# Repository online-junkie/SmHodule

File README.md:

# SmHodule

SmHodule is using the Wifi SoC ESP8266, the ESP8266 is a System on Chip and is as powerful as an Arduino.

SmHodule = Smart Home module for the Internet of Things.

This module is based on a set of examples found in the Internet about ESP8266 and implementing a actor, sender, sensor and I2C OLED.

The Setup data is cached in the modules flash memory.

Feel free to expand SmHodule and add your own ideas.

## Compile

Compile the code, then: make clean, make html, make all, make flashall
 
For first time setup keep GPIO15 pulled to ground for 35 seconds.
After first time configuration the module reboots and starts as an Access Point. Connect your wifi network to the new AP and use the default AP IP: 192.168.4.1 in your browser to access the module. Note: Your local router has to be DHCP enabled.

The device MAC and also the IP the module receives is shown on the SmHodule setup page. Make this IP static DHCP by using the modules name as the device name for your DHCP configuration.

Enjoy

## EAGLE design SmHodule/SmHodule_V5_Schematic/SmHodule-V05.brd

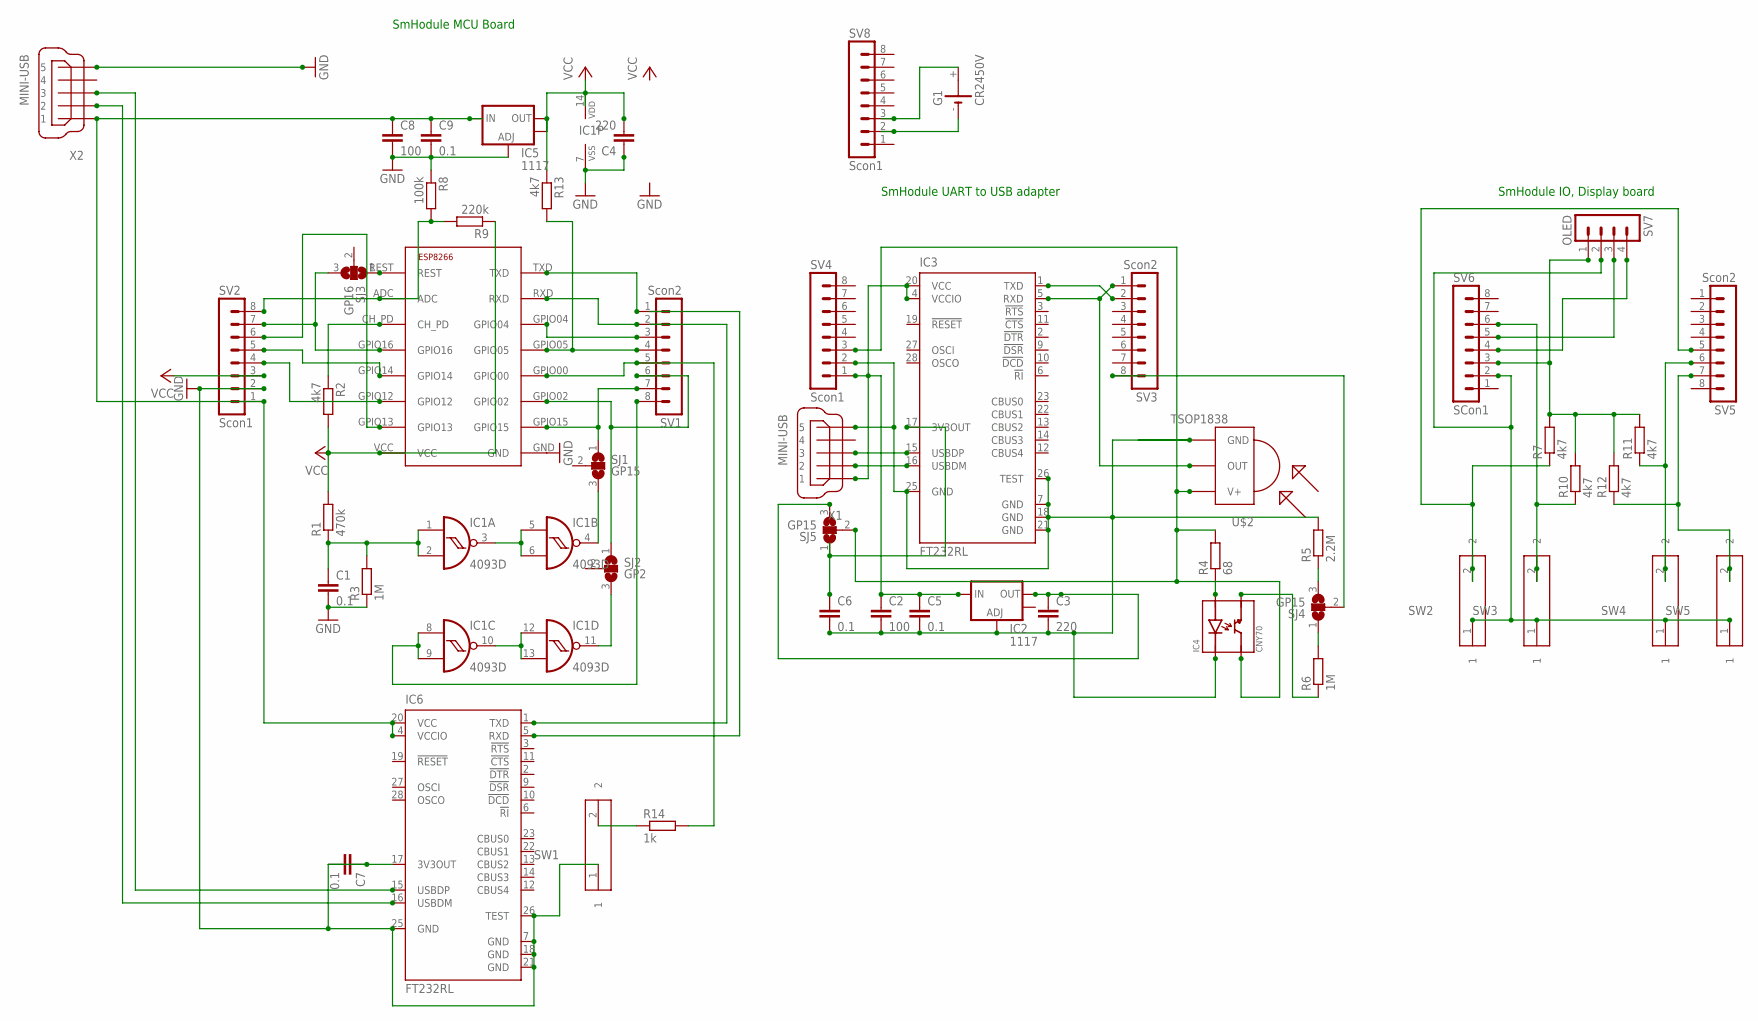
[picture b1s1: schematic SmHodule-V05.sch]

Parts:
C1, C5, C6, C7, C9: 0.1; C0805
C2, C8: 100; C1210
C3, C4: 220; C1210
G1: CR2450V
IC1: 4093D; SO14
IC2, IC5: 1117; SOT223
IC3, IC6: FT232RL; SSOP28
IC4: CNY70
R1: 470k; R0603
R2, R7, R10, R11, R12, R13: 4k7; R0603
R3, R6: 1M; R0603
R4: 68; R0603
R5: 2.2M; R0603
R8: 100k; R0603
R9: 220k; R0603
R14: 1k; R0603
SJ1, SJ4, SJ5: GP15; SJ_2
SJ2: GP2; SJ_2
SJ3: GP16; SJ_2
SV1, SV3, SV5: Scon2; MA08-1
SV2, SV4, SV8: Scon1; MA08-1
SV6: SCon1; MA08-1
SV7: OLED; MA04-1
SW1, SW2, SW3, SW4, SW5: 434111043826
U$1: ESP1; ESP-12
U$2: TSOP1838; TSOP18XX
X1, X2: MINI-USB; UX60-MB-5ST

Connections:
GND: C1.2, C4.1, C7.2, C8.2, C9.2, IC1.7 (VSS), IC5.1 (ADJ), IC6.7 (GND), IC6.18 (GND), IC6.21 (GND), IC6.25 (GND), IC6.26 (TEST), R3.1, R8.1, SV2.2, SW1.1, U$1.GND, X2.5
unnamed: C1.1, IC1.1 (I0), IC1.2 (I1), R1.1, R3.2
unnamed: IC1.3 (O), IC1.5 (I0), IC1.6 (I1)
unnamed: IC3.1 (TXD), SV3.2
unnamed: IC1.10 (O), IC1.12 (I0), IC1.13 (I1)
unnamed: IC1.4 (O), SJ1.3
unnamed: SV1.1, U$1.TXD
unnamed: SV1.2, U$1.RXD
unnamed: SV2.6, U$1.GPIO13
unnamed: R14.2, SV1.5, U$1.GPIO00
unnamed: SV2.4, U$1.GPIO12
unnamed: SV2.5, U$1.GPIO14
unnamed: SV1.3, U$1.GPIO04
unnamed: R13.2, SV1.4, U$1.GPIO05
unnamed: SJ3.3, SV2.7, U$1.GPIO16
unnamed: R6.2, SJ4.1
unnamed: R8.2, R9.2, SV2.8, U$1.ADC
unnamed: R2.1, U$1.CH_PD
unnamed: SJ1.1, SV1.7, U$1.GPIO15
unnamed: IC3.5 (RXD), SV3.1, U$2.OUT
unnamed: C2.2, C3.2, C5.2, C6.2, IC2.1 (ADJ), IC3.7 (GND), IC3.18 (GND), IC3.21 (GND), IC3.25 (GND), IC3.26 (TEST), IC4.EK, R5.2, SV4.2, U$2.GND, X1.5
unnamed: IC1.11 (O), SJ2.3
unnamed: SJ2.1, SV1.6, U$1.GPIO02
unnamed: SJ3.1, U$1.REST
unnamed: IC1.8 (I0), IC1.9 (I1), SV1.8
unnamed: IC4.DC, R4.2, SJ5.2, SV4.3, U$2.VCC (V+)
unnamed: C2.1, C5.1, IC2.3 (IN), IC3.4 (VCCIO), IC3.20 (VCC), SV4.1, X1.1
unnamed: R7.2, R10.2, R11.2, R12.2, SV6.3, SV7.1
unnamed: R11.1, SV5.6, SW4.2
unnamed: IC4.DE, R6.1
unnamed: R5.1, SJ4.3
unnamed: SV6.5, SV7.3
unnamed: R10.1, SV6.6, SW3.2
unnamed: R14.1, SW1.2
unnamed: IC4.EA, R4.1
unnamed: IC3.16 (USBDM), X1.2
unnamed: IC3.15 (USBDP), X1.3
unnamed: C6.1, IC3.17 (3V3OUT), SJ5.1
unnamed: R7.1, SV5.5, SW2.2
unnamed: SV6.4, SV7.4
unnamed: R12.1, SV5.7, SW5.2
unnamed: C3.1, IC2.2 (OUT), SJ5.3
unnamed: SV6.2, SV7.2, SW2.1, SW3.1, SW4.1, SW5.1
unnamed: SJ4.2, SV3.8
unnamed: G1.-, SV8.2
unnamed: G1.+, SV8.3
unnamed: C8.1, C9.1, IC5.3 (IN), IC6.4 (VCCIO), IC6.20 (VCC), SV2.1, X2.1
unnamed: IC6.15 (USBDP), X2.3
unnamed: IC6.16 (USBDM), X2.2
unnamed: C7.1, IC6.17 (3V3OUT)
VCC: C4.2, IC1.14 (VDD), IC5.2 (OUT), IC5.4 (OUT), R1.2, R2.2, R9.1, R13.1, SV2.3, U$1.VCC

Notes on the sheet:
SmHodule MCU Board
SmHodule UART to USB adapter
SmHodule IO, Display board

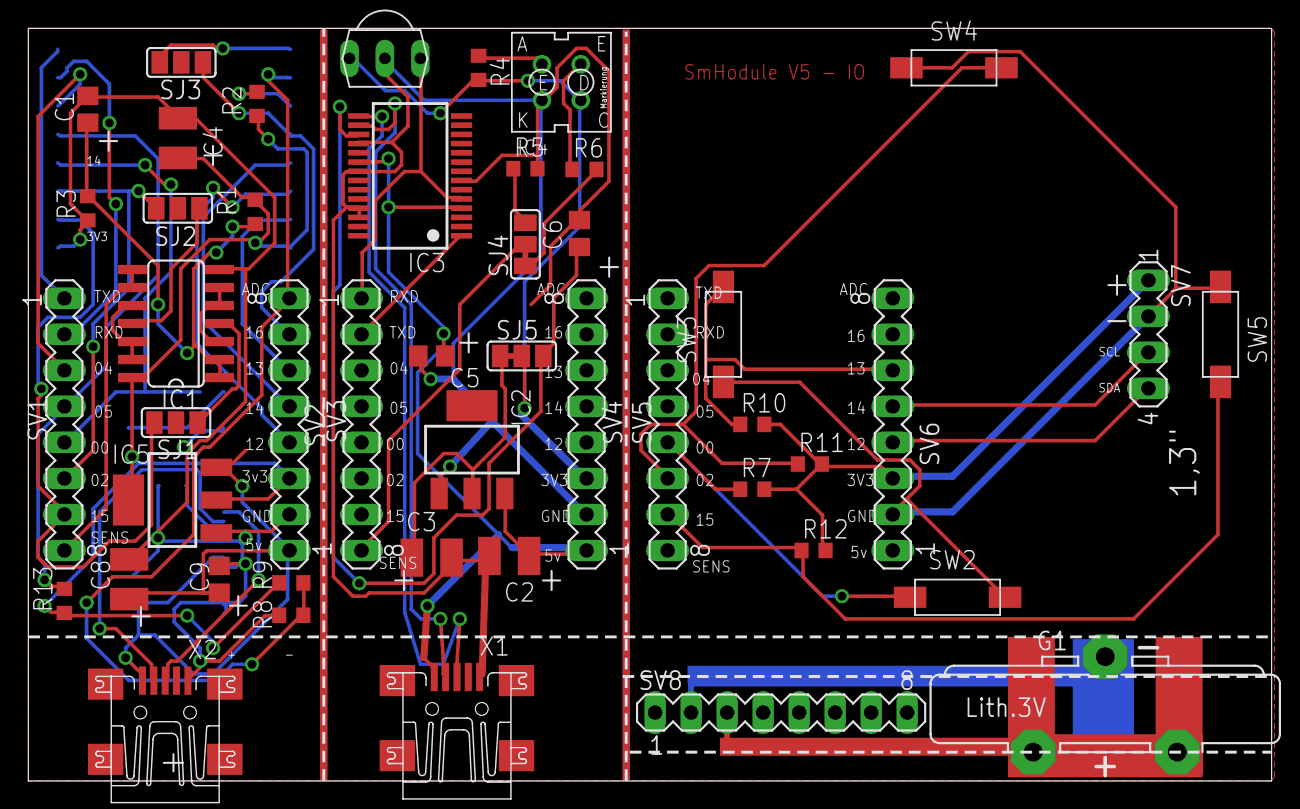
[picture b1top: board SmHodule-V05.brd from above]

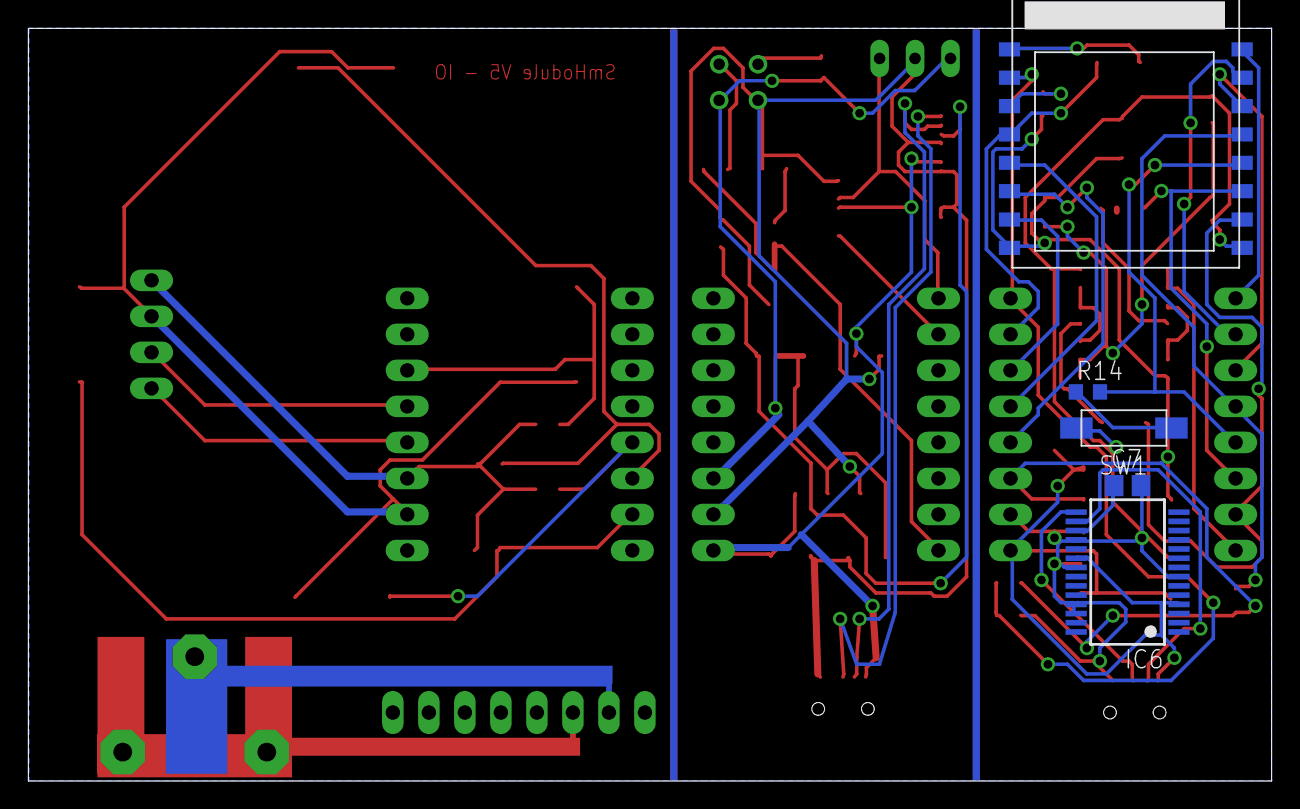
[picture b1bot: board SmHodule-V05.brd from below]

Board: 2 copper layers, 87.7 x 53.1 mm, 52 parts (5 on the bottom side), 51 nets.

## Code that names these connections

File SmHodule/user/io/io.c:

/*
 * ----------------------------------------------------------------------------
 * "THE BEER-WARE LICENSE" (Revision 42):
 * Jeroen Domburg <jeroen@spritesmods.com> wrote this file. As long as you retain 
 * this notice you can do whatever you want with this stuff. If we meet some day, 
 * and you think this stuff is worth it, you can buy me a beer in return. 
 * ----------------------------------------------------------------------------
 */


#include "c_types.h"
#include "user_interface.h"
#include "espconn.h"
#include "mem.h"
#include "osapi.h"
#include "gpio.h"
#include "io/gpio16.h"
#include "wifi/wifi.h"
#include "espmissingincludes.h"
#include "smhodule.h"
#include "io/io.h"
#include "i2c/i2c.h"
#include "i2c/i2c_oled.h"
#include "i2c/i2c_bmp180.h"

#define BTNDOWNGPIO 15
#define BTNUPGPIO 13
#define BTNRIGHTGPIO 2
#define BTNLEFTGPIO 0

static volatile bool OLED;
static ETSTimer resetBtnDwntimer;
static ETSTimer resetBtnUptimer;
static ETSTimer resetBtnLefttimer;
static ETSTimer resetBtnRighttimer;
static int fontsize = 2;
uint32 stime0 = 0, stime1 = 0;
static uint16_t gpio13_counter = 0;                        // gpio13 counter

void ICACHE_FLASH_ATTR ioGPIO16(int ena) {
	if (ena) {
		gpio16_output_set(1);
		if ( atoi(Setup.OLED) == 1 )
			OLED_Print(1,(1*fontsize),"GPIO16:on ",fontsize); // x,y,text,fontsize -> y need to be 2*fontsize
	} else {
		gpio16_output_set(0);
		if ( atoi(Setup.OLED) == 1 )
			OLED_Print(1,(1*fontsize),"GPIO16:off",fontsize);
	}
}

static void ICACHE_FLASH_ATTR resetBtnUpTimerCb(void *arg) {
	static int resetCnt=0;
	if (!GPIO_INPUT_GET(BTNUPGPIO)) {
		resetCnt++;
		os_printf("UP Cnt: %d\n", resetCnt);
	} else {
		if (resetCnt>=3 ) { //>200msec pressed
			sendKeyData(2,resetCnt,1); // long
			os_printf("Key UP pressed long\n");
		} else if (resetCnt>=1 && resetCnt <=2 ) { //<200msec pressed
			sendKeyData(2,0,1); //short
			os_printf("Key UP pressed short\n");
		}
		resetCnt=0;
	}
}

static void ICACHE_FLASH_ATTR resetBtnLeftTimerCb(void *arg) {
	static int resetCnt=0;
	if (!GPIO_INPUT_GET(BTNLEFTGPIO)) {
		resetCnt++;
		os_printf("Left cnt: %d\n", resetCnt);
	} else {
		if (resetCnt > 40) { //>8 sec pressed and clear config
			setup_wifi_ap_mode();
			initSetupData();
		} else if (resetCnt>=3 && resetCnt<=40) { //<8 sec pressed
			sendKeyData(4,resetCnt,2); // long
			os_printf("Key Left pressed long\n");
		} else if (resetCnt>=1 && resetCnt <=2 ) { //<200msec pressed
			sendKeyData(4,0,2); //short
			os_printf("Key Left pressed short\n");
		}
		resetCnt=0;
	}
}

static void ICACHE_FLASH_ATTR resetBtnRightTimerCb(void *arg) {
	static int resetCnt=0;
	if (!GPIO_INPUT_GET(BTNRIGHTGPIO)) {
		resetCnt++;
		os_printf("Right cnt: %d\n", resetCnt);
	} else {
		if (resetCnt>=3) { //>200msec pressed
			sendKeyData(3,resetCnt,3); // long
			os_printf("Key RIGHT pressed long\n");
		} else if (resetCnt>=1 && resetCnt <=2 ) { //<200msec pressed
			sendKeyData(3,0,3); //short
			os_printf("Key RIGHT pressed short\n");
		}
		resetCnt=0;
	}
}

static void ICACHE_FLASH_ATTR resetBtnDwnTimerCb(void *arg) {
	static int resetCnt=0;
	if (!GPIO_INPUT_GET(BTNDOWNGPIO)) {
		resetCnt++;
		os_printf("DOWN resetCnt: %d\n", resetCnt);
	} else {
		if (resetCnt>=3) { //>=200msec pressed
			sendKeyData(1,resetCnt,0); // long
			os_printf("Key DOWN pressed long\n");
		} else if (resetCnt>=1 && resetCnt <=2 ) { //<200 msec pressed
			sendKeyData(1,0,0); //short
			os_printf("Key DOWN pressed short\n");
		}
		resetCnt=0;
	}
}

static void ICACHE_FLASH_ATTR gpio13_int_handler(int8_t key) // key not right used
{
	ETS_GPIO_INTR_DISABLE();  										// Disable gpio interrupts
	// Increment counter
    gpio13_counter++;
    //Not that sure what this does yet and where the register is used for
    uint32 gpio_status = GPIO_REG_READ(GPIO_STATUS_ADDRESS);
    //clear interrupt status
    GPIO_REG_WRITE(GPIO_STATUS_W1TC_ADDRESS, gpio_status & BIT(key));
    ETS_GPIO_INTR_ENABLE();                                         // Enable gpio interrupts
}

void ICACHE_FLASH_ATTR gpio13_int_prepare(void)
{
	// prepare GPIO13 to handle interrupts
	ETS_GPIO_INTR_DISABLE();  										// Disable gpio interrupts
	ETS_GPIO_INTR_ATTACH(gpio13_int_handler, 13);                   // GPIO13 interrupt handler
	PIN_FUNC_SELECT(PERIPHS_IO_MUX_MTCK_U, FUNC_GPIO13);            // Set GPIO13 function
	gpio_output_set(0, 0, 0, GPIO_ID_PIN(13));                       // Set GPIO13 as input
	GPIO_REG_WRITE(GPIO_STATUS_W1TC_ADDRESS, BIT(13));               // Clear GPIO13 status
	gpio_pin_intr_state_set(GPIO_ID_PIN(13), GPIO_PIN_INTR_POSEDGE); // Interrupt on GPIO13
	PIN_PULLUP_DIS(PERIPHS_IO_MUX_MTCK_U);                          // Disabe pullup
	ETS_GPIO_INTR_ENABLE();                                         // Enable gpio interrupts
}

uint16_t ICACHE_FLASH_ATTR getGpio13Counter(void) {
	return gpio13_counter;
}

void ICACHE_FLASH_ATTR resetGpio13Counter(void) {
	gpio13_counter = 0;
}

void ioInit() {
	bool isInitialized = 0;
	gpio_init();
	// validate if possible because during boot GPIO0 and GPIO15 need to be low level

    // 12 and 14 should be used for I2C bus
	// this are the two pins we're going to use
    // gpio12 (sda), 14 (scl) are used as i2c
	if ( atoi(Setup.OLED) == 1 ) {
		i2c_init();
		isInitialized = 1;
		OLED = OLED_Init();
		OLED_Print(0, 0, getSmHoduleName(), fontsize);
	}
	if ( atoi(Setup.BMP180) == 1 ) {
		if ( !isInitialized)
			i2c_init();
		BMP180_Init();
	}
	// dangerous, use only if gpio16 is not bridged with rst
	// use this module as an actor
	if ( atoi((uint8_t *) Setup.Type) >= 3 ) {
		// SmHodule is used as an actor -> GPIO16
		gpio16_output_conf();
		gpio16_output_set(0);
	} else if ( atoi((uint8_t *) Setup.Type) == 2 ) {
		// SmHodule is used as a sender...
		//gpio16_output_set(1);

		// Key Right GPIO2
		PIN_FUNC_SELECT(PERIPHS_IO_MUX_GPIO2_U, FUNC_GPIO2);
		os_timer_disarm(&resetBtnRighttimer);
		os_timer_setfn(&resetBtnRighttimer, resetBtnRightTimerCb, NULL);
		os_timer_arm(&resetBtnRighttimer, 100, 1);

		// Key Up GPIO13
		PIN_FUNC_SELECT(PERIPHS_IO_MUX_MTCK_U, FUNC_GPIO13);
		os_timer_disarm(&resetBtnUptimer);
		os_timer_setfn(&resetBtnUptimer, resetBtnUpTimerCb, NULL);
		os_timer_arm(&resetBtnUptimer, 100, 1);

		// Key Left GPIO0
		PIN_FUNC_SELECT(PERIPHS_IO_MUX_GPIO0_U, FUNC_GPIO0);
		os_timer_disarm(&resetBtnLefttimer);
		os_timer_setfn(&resetBtnLefttimer, resetBtnLeftTimerCb, NULL);
		os_timer_arm(&resetBtnLefttimer, 100, 1);
	} else {
		// SmHodule is used as a sensor
		// if used as a sensor, then gpio13 is used to count events
		// basically a 10sec measurement and then value is send to host
		gpio13_int_prepare();  // for interrupt
	}

	// By default GPIO 15 is used to reset module incl. wifi
	//key Dwn GPIO15
	PIN_FUNC_SELECT(PERIPHS_IO_MUX_MTDO_U, FUNC_GPIO15);
	os_timer_disarm(&resetBtnDwntimer);
	os_timer_setfn(&resetBtnDwntimer, resetBtnDwnTimerCb, NULL);
	os_timer_arm(&resetBtnDwntimer, 100, 1);
}

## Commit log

2015-04-03 SmHodule
2015-08-15 Changes to: - Initializing SmHodule - SDK 1.0
2015-08-15 Minor fixes - first init, defaults name to SmHodul-<mac>
2015-08-16 Update: 16.08.2015
2015-08-16 Solved problem with TcpClient closing connection
2015-08-16 Fix for Display board, keys are now in reverse but correct order.
2015-10-30 Now includes all Eagle Files
2015-10-30 Eagle files

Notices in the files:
parts and their libraries:
Kurzhubtaster: Copyright: WÃÂ¼rth Elektronik
Kurzhubtaster: Copyright: Würth Elektronik
